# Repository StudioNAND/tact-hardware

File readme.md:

# Tact Hardware

Tact sensor schematics - electronic circuits that enable experiments with capacitive sensing.

----

This project belongs to the following repositories:

* **[Tact Arduino sketches](https://github.com/StudioNAND/tact-arduino-sketch)** and **[Tact Arduino library](https://github.com/philippschmitt/tact-arduino)** (by Philipp Schmitt) to drive circuit interface. Those scripts are for handling serial requests and serving sensor data.
* **[Tact for Processing](https://github.com/StudioNAND/tact-processing/)** for retrieving and processing sensor data in an easy manner.

## Circuit

The Tact circuit is based on Mads Hobye's capacitive touch [Arduino Tutorial](http://www.instructables.com/id/Touche-for-Arduino-Advanced-touch-sensing/step1/Components-neded/). You will need the following components to set up a basic version:

* 1× 1N4148 diode
* 1× 10mH coil

Condensators

* 1× 100pF
* 1× 10nF

Resistors

* 1× 3,3k
* 1× 10k
* 1× 1M

The following [Frizing](http://fritzing.org/home/) sketches illustrate how to set up a Tact sensor. Each of them are kept as simple as possible, essentially only requireing a breadboard and jumper wires to hookup everything to the Arduino.

#### Single Sensor Setup

[Download](https://github.com/StudioNAND/tact-hardware/raw/master/tactA_breadboard_single/tactA_breadboard_single.fzz) the Fritzing sketch - or browse the corresponding [project folder](https://github.com/StudioNAND/tact-hardware/tree/master/tactA_breadboard_single) in this repository.

#### Multiplexed Sensor Setup

[Download](https://github.com/StudioNAND/tact-hardware/raw/master/tactA_breadboard_multiplex/tactA_breadboard_multiplex.fzz) the Fritzing sketch for detailed investigation - or check the corresponding [project folder](https://github.com/StudioNAND/tact-hardware/tree/master/tactA_breadboard_multiplex) in this repository.

### Source
All source files that are required to modify and extend circuits are contained within th download and also available on [github](tree/master/src).

### Questions?
Any questions or feedback? Contact me on [twitter](http://www.twitter.com/steffen_fiedler). For bug reports, please use the [issue tracker](issues).

## Who made this?
The material in this repository has been developed by [Studio NAND](http://www.nand.io). It’s based on many smart ideas – so cheers to everyone who contributed her/his time to investigate capacitive technology! Special thanks to the team around [Ivan Poupyrev](http://www.ivanpoupyrev.com/) for all the research within this field and [Mads Hobye](http://www.hobye.dk/) for his [Arduino tutorial](http://www.instructables.com/id/Touche-for-Arduino-Advanced-touch-sensing/) about advanced touch sensing. All of that has been a big help and inspiration.

## Copyright
Copyright (c) 2014 [Studio NAND](http://www.nand.io). Licensed under the GNU Lesser General Public License. See *license.txt* for further details.

Any example code is released into the public domain.

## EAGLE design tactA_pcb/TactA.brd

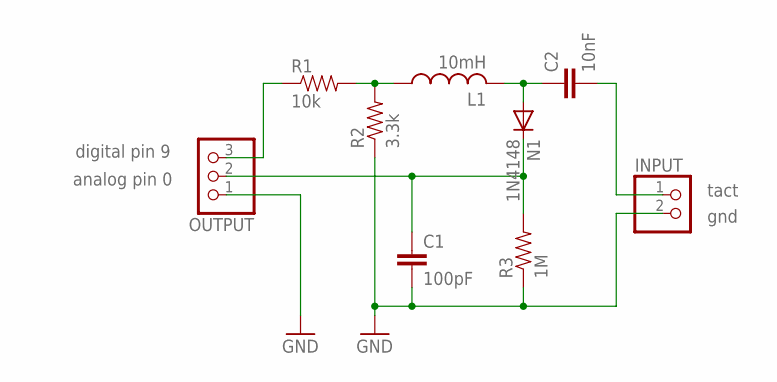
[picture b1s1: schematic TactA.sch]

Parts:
C1: 100pF; CAP-PTH-SMALL
C2: 10nF; CAP-PTH-SMALL
INPUT: PINHD-1X2; 1X02
L1: 10mH; 6000-XXXX-RC
N1: 1N4148; DO35-7
OUTPUT: PINHD-1X3; 1X03
R1: 10k; AXIAL-0.4
R2: 3.3k; AXIAL-0.4
R3: 1M; AXIAL-0.4

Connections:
A0: C1.1, N1.C, OUTPUT.2, R3.P$2 (2)
D9: OUTPUT.3, R1.P$1 (1)
GND: C1.2, INPUT.2, OUTPUT.1, R2.P$1 (1), R3.P$1 (1)
unnamed: L1.1, R1.P$2 (2), R2.P$2 (2)
unnamed: C2.1, L1.2, N1.A
TACTSENSE: C2.2, INPUT.1

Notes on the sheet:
tact
gnd
digital pin 9
analog pin 0

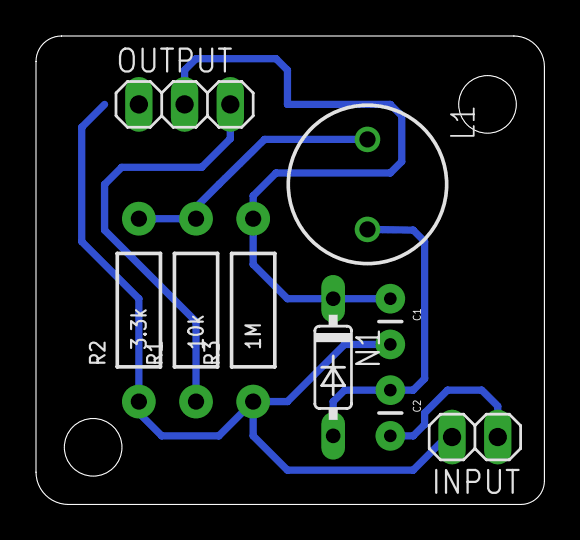
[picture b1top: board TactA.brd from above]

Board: 2 copper layers, 28.2 x 26.0 mm, 9 parts (0 on the bottom side), 6 nets.

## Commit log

2014-10-23 inital commit
2014-10-23 adds TactA single sensor breadboard project
2014-10-23 adds TactA multiplex sensor breadboard project
2014-10-24 adds TactA single sensor pcb project
2014-10-24 updates readme

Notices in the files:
parts and their libraries:
SparkFun-Passives: Licensing: CC v3.0 Share-Alike You are welcome to use this library for commercial purposes.
